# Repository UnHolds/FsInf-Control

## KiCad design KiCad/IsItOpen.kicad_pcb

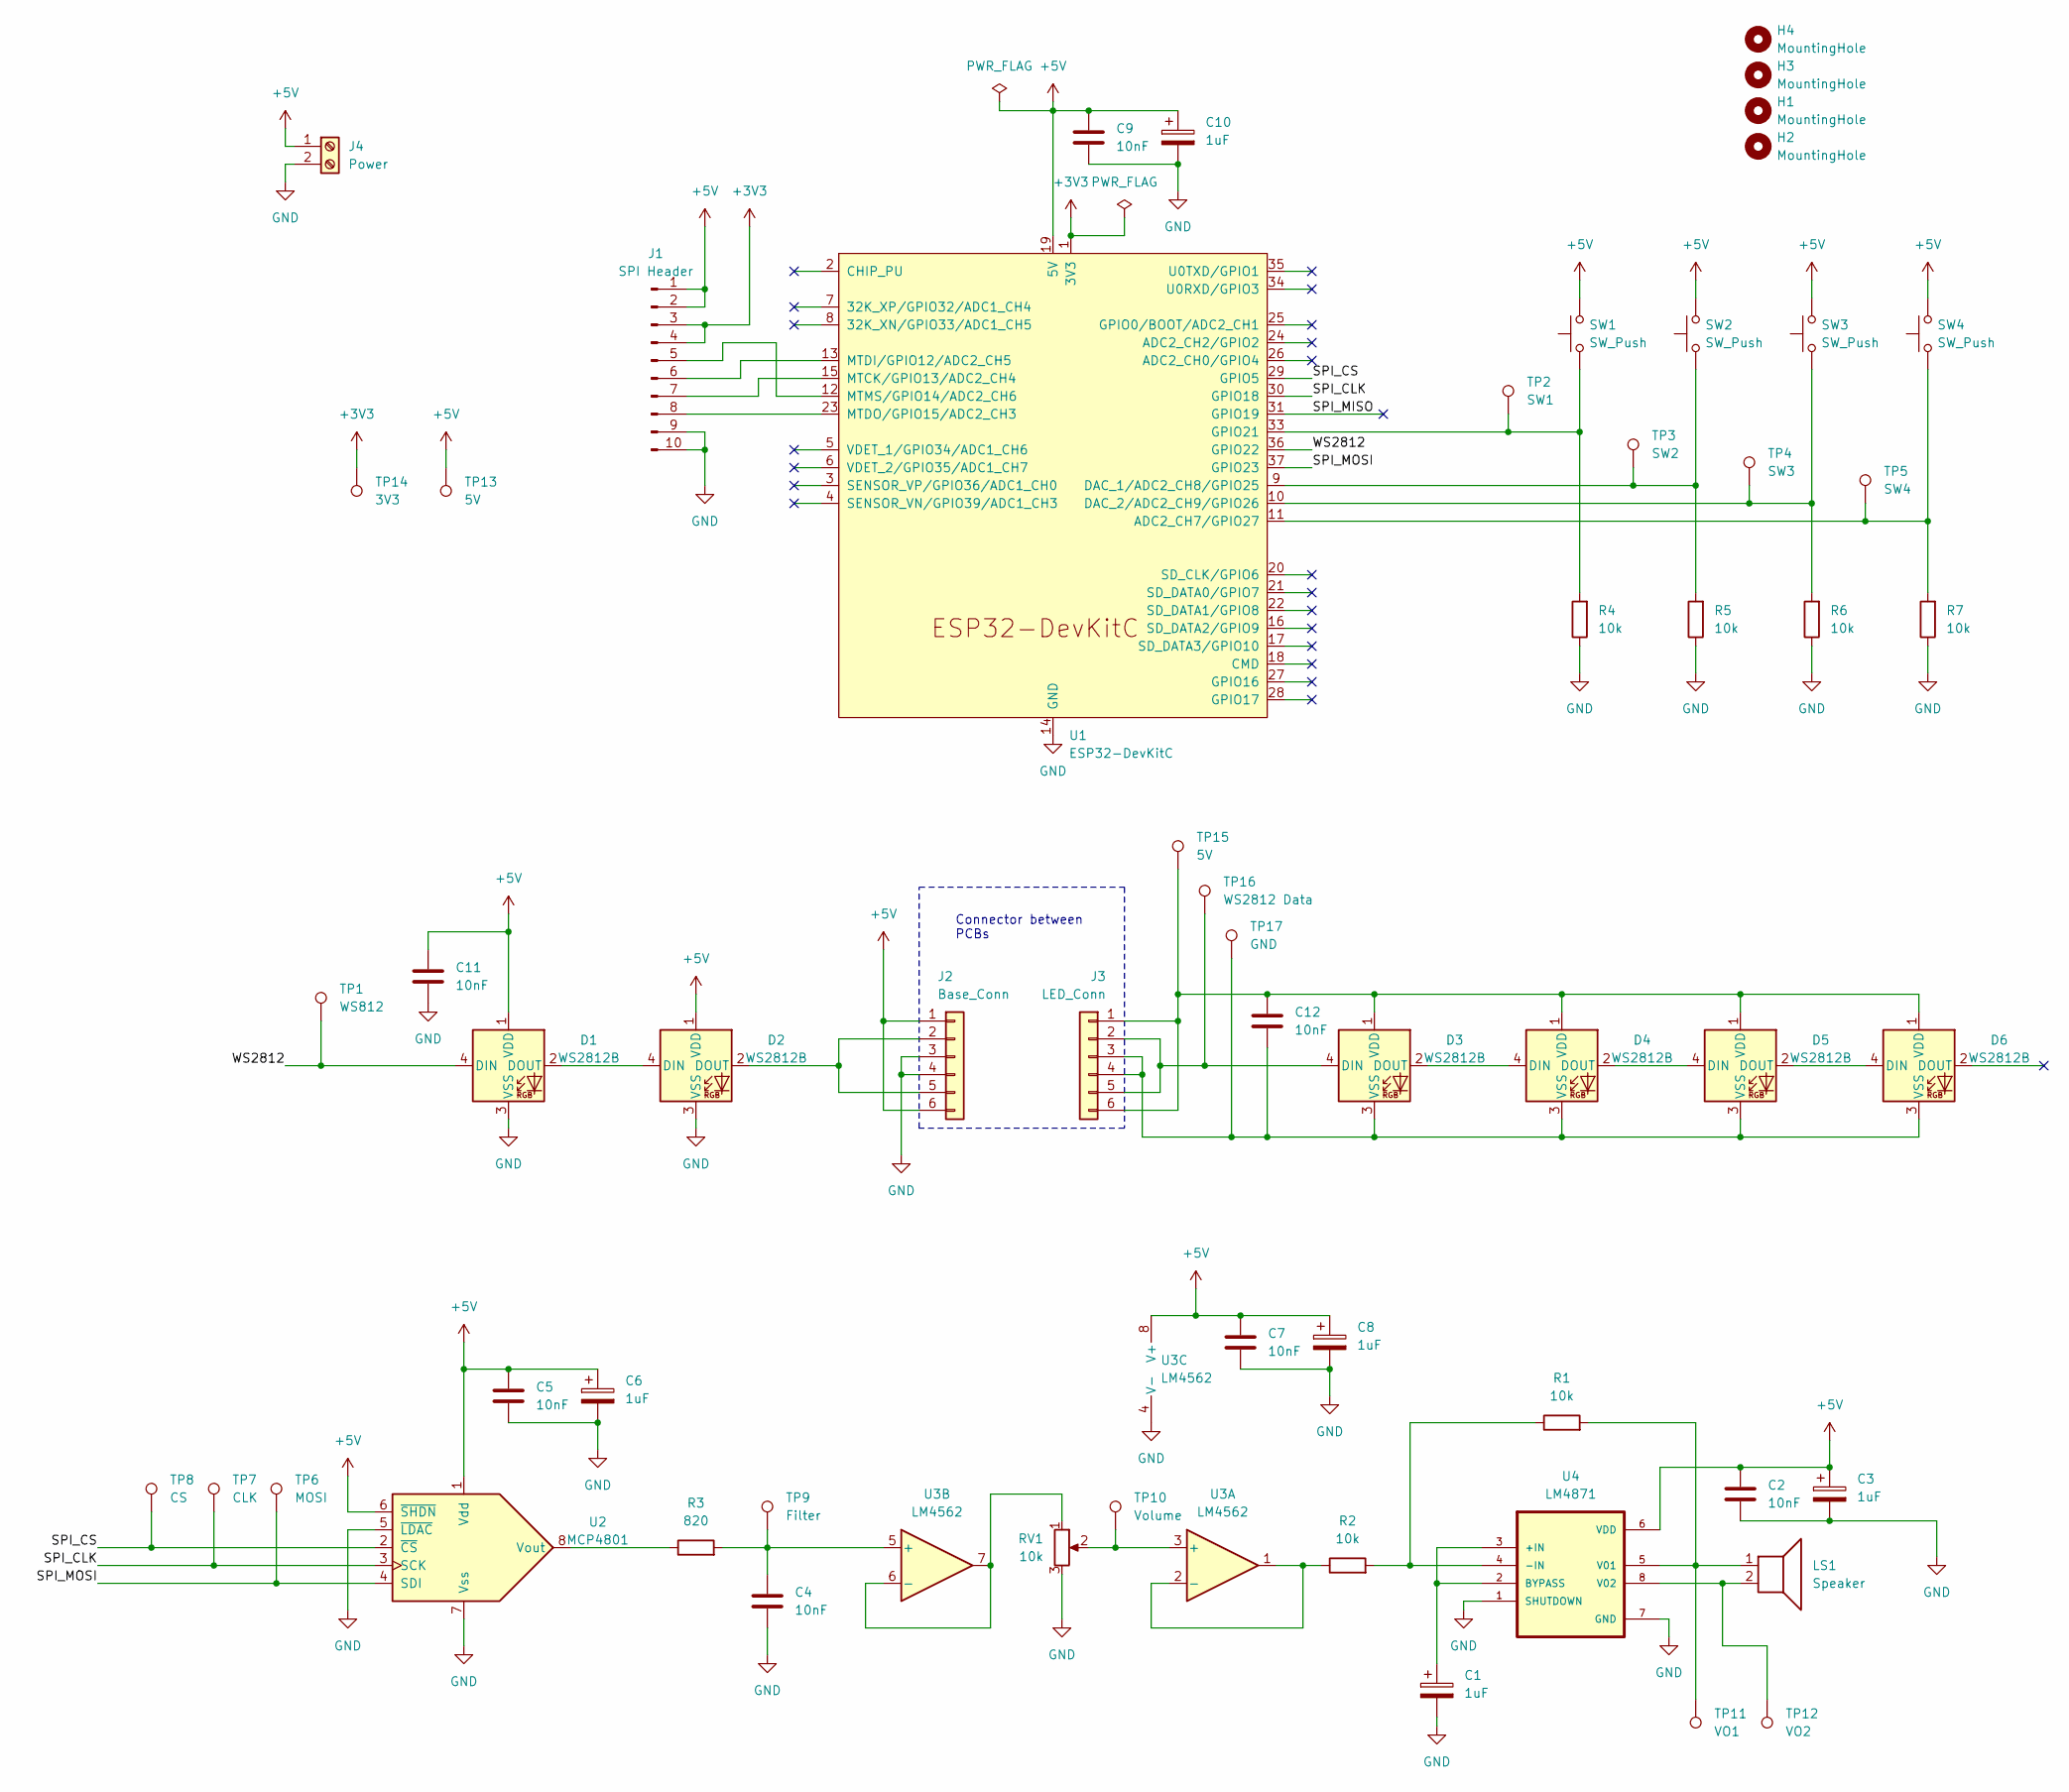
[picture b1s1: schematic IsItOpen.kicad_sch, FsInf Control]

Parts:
C1, C3, C6, C8, C10: 1uF; CP_Radial_D5.0mm_P2.50mm
C2, C4, C5, C7, C9, C11, C12: 10nF; C_1206_3216Metric_Pad1.33x1.80mm_HandSolder
D1, D2, D3, D4, D5, D6: WS2812B; LED_WS2812B_PLCC4_5.0x5.0mm_P3.2mm
H1, H2, H3, H4: MountingHole; MountingHole_3.2mm_M3
J1: SPI Header; PinHeader_1x10_P2.54mm_Vertical
J2: Base_Conn; BasePCB
J3: LED_Conn; LedPCB
J4: Power; TerminalBlock_MetzConnect_Type055_RT01502HDWU_1x02_P5.00mm_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
LS1: Speaker; PinHeader_1x02_P2.54mm_Vertical
R1, R2, R4, R5, R6, R7: 10k; R_0805_2012Metric_Pad1.20x1.40mm_HandSolder
R3: 820; R_0805_2012Metric_Pad1.20x1.40mm_HandSolder
RV1: 10k; Potentiometer_Piher_PT-6-V_Vertical
SW1, SW2, SW3, SW4: SW_Push; PinHeader_1x02_P2.54mm_Vertical
TP1: WS812; TestPoint_Pad_D3.0mm
TP2: SW1; TestPoint_Pad_D3.0mm
TP3: SW2; TestPoint_Pad_D3.0mm
TP4: SW3; TestPoint_Pad_D3.0mm
TP5: SW4; TestPoint_Pad_D3.0mm
TP6: MOSI; TestPoint_Pad_D3.0mm
TP7: CLK; TestPoint_Pad_D3.0mm
TP8: CS; TestPoint_Pad_D3.0mm
TP9: Filter; TestPoint_Pad_D3.0mm
TP10: Volume; TestPoint_Pad_D3.0mm
TP11: VO1; TestPoint_Pad_D3.0mm
TP12: VO2; TestPoint_Pad_D3.0mm
TP13, TP15: 5V; TestPoint_Pad_D3.0mm
TP14: 3V3; TestPoint_Pad_D3.0mm
TP16: WS2812 Data; TestPoint_Pad_D3.0mm
TP17: GND; TestPoint_Pad_D3.0mm
U1: ESP32-DevKitC
U2: MCP4801; DIP-8_W7.62mm
U3: LM4562; DIP-8_W7.62mm
U4: LM4871; SOIC-8_5.23x5.23mm_P1.27mm

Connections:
+3V3: J1.3, J1.4, TP14.1, U1.1 (3V3)
+5V: C2.1, C3.1, C5.1, C6.1, C7.1, C8.1, C9.1, C10.1, C11.1, D1.1 (VDD), D2.1 (VDD), J1.1, J1.2, J2.1, J2.6, J4.1, SW1.2, SW2.2, SW3.2, SW4.2, TP13.1, U1.19 (5V), U2.1 (Vdd), U2.6 (~SHDN), U3.8 (V+), U4.6 (VDD)
/SPI_CLK: TP7.1, U1.30 (GPIO18), U2.3 (SCK)
/SPI_CS: TP8.1, U1.29 (GPIO5), U2.2 (~CS)
/SPI_MISO: U1.31 (GPIO19)
/SPI_MOSI: TP6.1, U1.37 (GPIO23), U2.4 (SDI)
/WS2812: D1.4 (DIN), TP1.1, U1.36 (GPIO22)
GND: C1.2, C2.2, C3.2, C4.2, C5.2, C6.2, C7.2, C8.2, C9.2, C10.2, C11.2, D1.3 (VSS), D2.3 (VSS), J1.9, J1.10, J2.3, J2.4, J4.2, R4.1, R5.1, R6.1, R7.1, RV1.3, U1.14 (GND), U1.32 (GND), U1.38 (GND), U2.5 (~LDAC), U2.7 (Vss), U3.4 (V-), U4.1 (SHUTDOWN), U4.7 (GND)
unnamed: D1.2 (DOUT), D2.4 (DIN)
unnamed: D2.2 (DOUT), J2.2, J2.5
unnamed: D3.4 (DIN), J3.2, J3.5, TP16.1
unnamed: D3.2 (DOUT), D4.4 (DIN)
unnamed: C12.1, D3.1 (VDD), D4.1 (VDD), D5.1 (VDD), D6.1 (VDD), J3.1, J3.6, TP15.1
unnamed: C12.2, D3.3 (VSS), D4.3 (VSS), D5.3 (VSS), D6.3 (VSS), J3.3, J3.4, TP17.1
unnamed: D4.2 (DOUT), D5.4 (DIN)
unnamed: D5.2 (DOUT), D6.4 (DIN)
unnamed: J1.5, U1.12 (MTMS/GPIO14/ADC2_CH6)
unnamed: J1.6, U1.13 (MTDI/GPIO12/ADC2_CH5)
unnamed: J1.7, U1.15 (MTCK/GPIO13/ADC2_CH4)
unnamed: J1.8, U1.23 (MTDO/GPIO15/ADC2_CH3)
unnamed: R7.2, SW4.1, TP5.1, U1.11 (ADC2_CH7/GPIO27)
unnamed: R5.2, SW2.1, TP3.1, U1.9 (DAC_1/ADC2_CH8/GPIO25)
unnamed: R6.2, SW3.1, TP4.1, U1.10 (DAC_2/ADC2_CH9/GPIO26)
unnamed: R4.2, SW1.1, TP2.1, U1.33 (GPIO21)
unnamed: R3.1, U2.8 (Vout)
unnamed: RV1.2, TP10.1, U3.3 (+)
unnamed: R2.1, U3.1, U3.2 (-)
unnamed: C4.1, R3.2, TP9.1, U3.5 (+)
unnamed: RV1.1, U3.6 (-), U3.7
unnamed: C1.1, U4.2 (BYPASS), U4.3 (+IN)
unnamed: R1.1, R2.2, U4.4 (-IN)
unnamed: LS1.1, R1.2, TP11.1, U4.5 (V01)
unnamed: LS1.2, TP12.1, U4.8 (V02)

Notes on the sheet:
Connector between PCBs

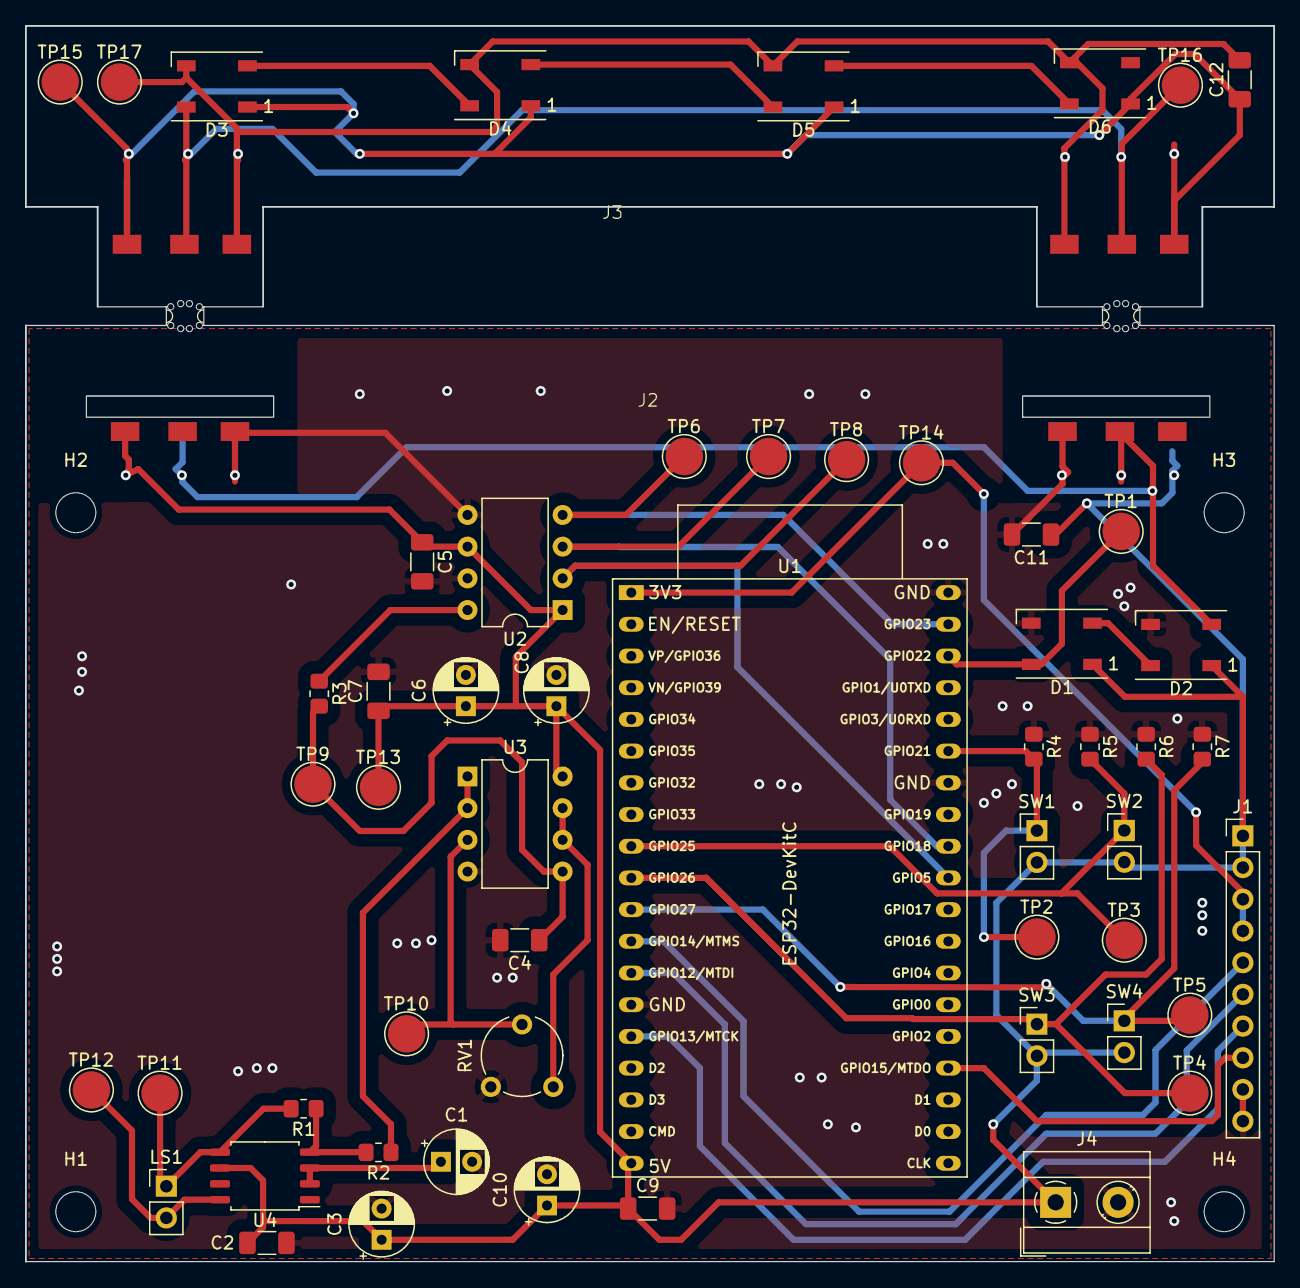
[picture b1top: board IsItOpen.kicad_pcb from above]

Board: 2 copper layers, 100.0 x 99.0 mm, 62 parts (0 on the bottom side), 32 nets.

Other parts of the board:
mouse-bite-1mm-slot, mouse-bite-1mm-slot#2: VAL**; mouse-bite-1mm-slot

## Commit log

2024-03-29 Added inital schematic
2024-03-30 added pcb connector
2024-04-20 added footprint for pcb connector
2024-04-20 added basic pcb layout
2024-04-28 routed pcbn
2024-05-18 fixed footprint + connected unconnected items
2024-05-18 added plots
2024-05-18 renamend kicad
2024-05-18 Added basic firmware files
2024-05-18 added basic firmware without serial
2024-05-18 added cad file for the housing
2024-05-19 added export for v1 + gitignore
2024-05-19 added fsinf logo
2024-05-20 update firmware
2024-05-20 removed wrong export file + update
2024-06-25 fixed small bug in serial read
2024-06-25 added basic backend
2024-06-25 added play + implemented backend
2024-06-26 added dim via UART + added shdn for speaker
2024-06-26 added light sleep mode
2024-06-27 mattermost support, replace " -> ', http errorcodes responses
2024-06-28 disabled sleep (brakes uart read)
2024-06-28 handle new firmware features
2024-07-01 added requirements.txt, and a simple config
2024-07-01 added a systemd service file

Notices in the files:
KiCad/IsItOpen.kicad_sch:
License: CERN-OHL-S
